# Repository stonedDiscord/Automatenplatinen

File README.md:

# Automatenplatinen
Alle möglichen Sachen die ich als Teil des Spielautomaten Hobby so nachgebaut habe.

Diskussionen rund um die Entwicklung führe ich generell auf dem Automatentreff Discord:
https://discord.gg/CEFa4MkQmW

Fertig sind:
- Initialisierer: ein Init-Stecker für weiße CPUs. Hat 2 Taster.
- ServiceTastaturWeissFake - das ist ein simpler Nachbau einer Servicetastatur für die weiße CPU. Dadurch das sie simpler ist, sind überall die Zahl 0 auf halber Helligkeit zu sehen. Verwenden lässt sie sich trotzdem.
- ZLKhalter: Anscheinend beraubt jeder, der Zulassungskarten beschreibt, einen Automaten um diesen Halter. Katastrophe.
- Zulassungskarte: Neuere mit Atmega48.

Die Gerber werde ich bei den Releases hochladen.

Ungetestet:
- FlashUniversal: Eine Pogo-Pin Platine für Datenbanken.
- LEDLamp: Das sind LEDs die in die Sockel dieser 6V 2W Glühbirnchen passen und einen Kondensator mit dabei haben damit sie langsam ausgehen wie die alten Birnen.
- LPTastatur: das ist die Tastatur für einen NSM Drucker.
- NSMAdapter: Ein Adapter der die Pins vom Timekeeper auf NSM Spielmodulen so nach außen führt das man sie mit einem EEPROM Brenner beschreiben kann.
- PCauslese: Ein Auslese-Adapter mit einem ESP-01. Soll kompatibel mit den ganz alten Geräten werden und die Uhrzeit automatisch setzen und die ausgelesenen Daten zwischenspeichern.
- ProgrammierStation: Arduino ISP Programmer und Seriell auf einem Board mit Stromversorgung.
- ST25: Tastatur für NSM Geräte
- SoundkartenProg: Ein Inverter für den seriellen Anschluss von kleinen Soundkarten.
- Tasterplatine: Fast das gleiche wie die LEDLamp aber mit einem Taster dabei. Für alte Geräte mit weißer CPU.
- Soundkarte: Ein Inverter für TTL-Signale um kleine Soundkarten auszulesen/beschreiben
- ZLKalt: Zulassungskarte mit AT90

Schrott:
- DB1MBRedesign: Forschung wo die Pins der Datenbank hingehen.
- DBV: Das ist ein Stecker der in den CPU-Sockel von Bally Wulff Spielmodulen kommt und dann die RTC und den SRAM beschreiben kann, ähnlich dem Datenbankverwalter
- E60: Hier wollt ich mal schauen wie die Konvertierung der Logik-Level umgesetzt wurde. Das Ergebnis: Ein Transistor halt. Naja.
- Programmierboard: Ein User hat das Ding auf eBay geschossen und wollte wissen was es kann.
- Serial: die ProgrammierStation aber mit WLAN, liegt auf Eis bis die normale ProgrammierStation fertig ist.
- Spielmodul: Forschung für den DBV wo die ganzen Leiterbahnen eigentlich hingehen und wie man den RTC anspricht.

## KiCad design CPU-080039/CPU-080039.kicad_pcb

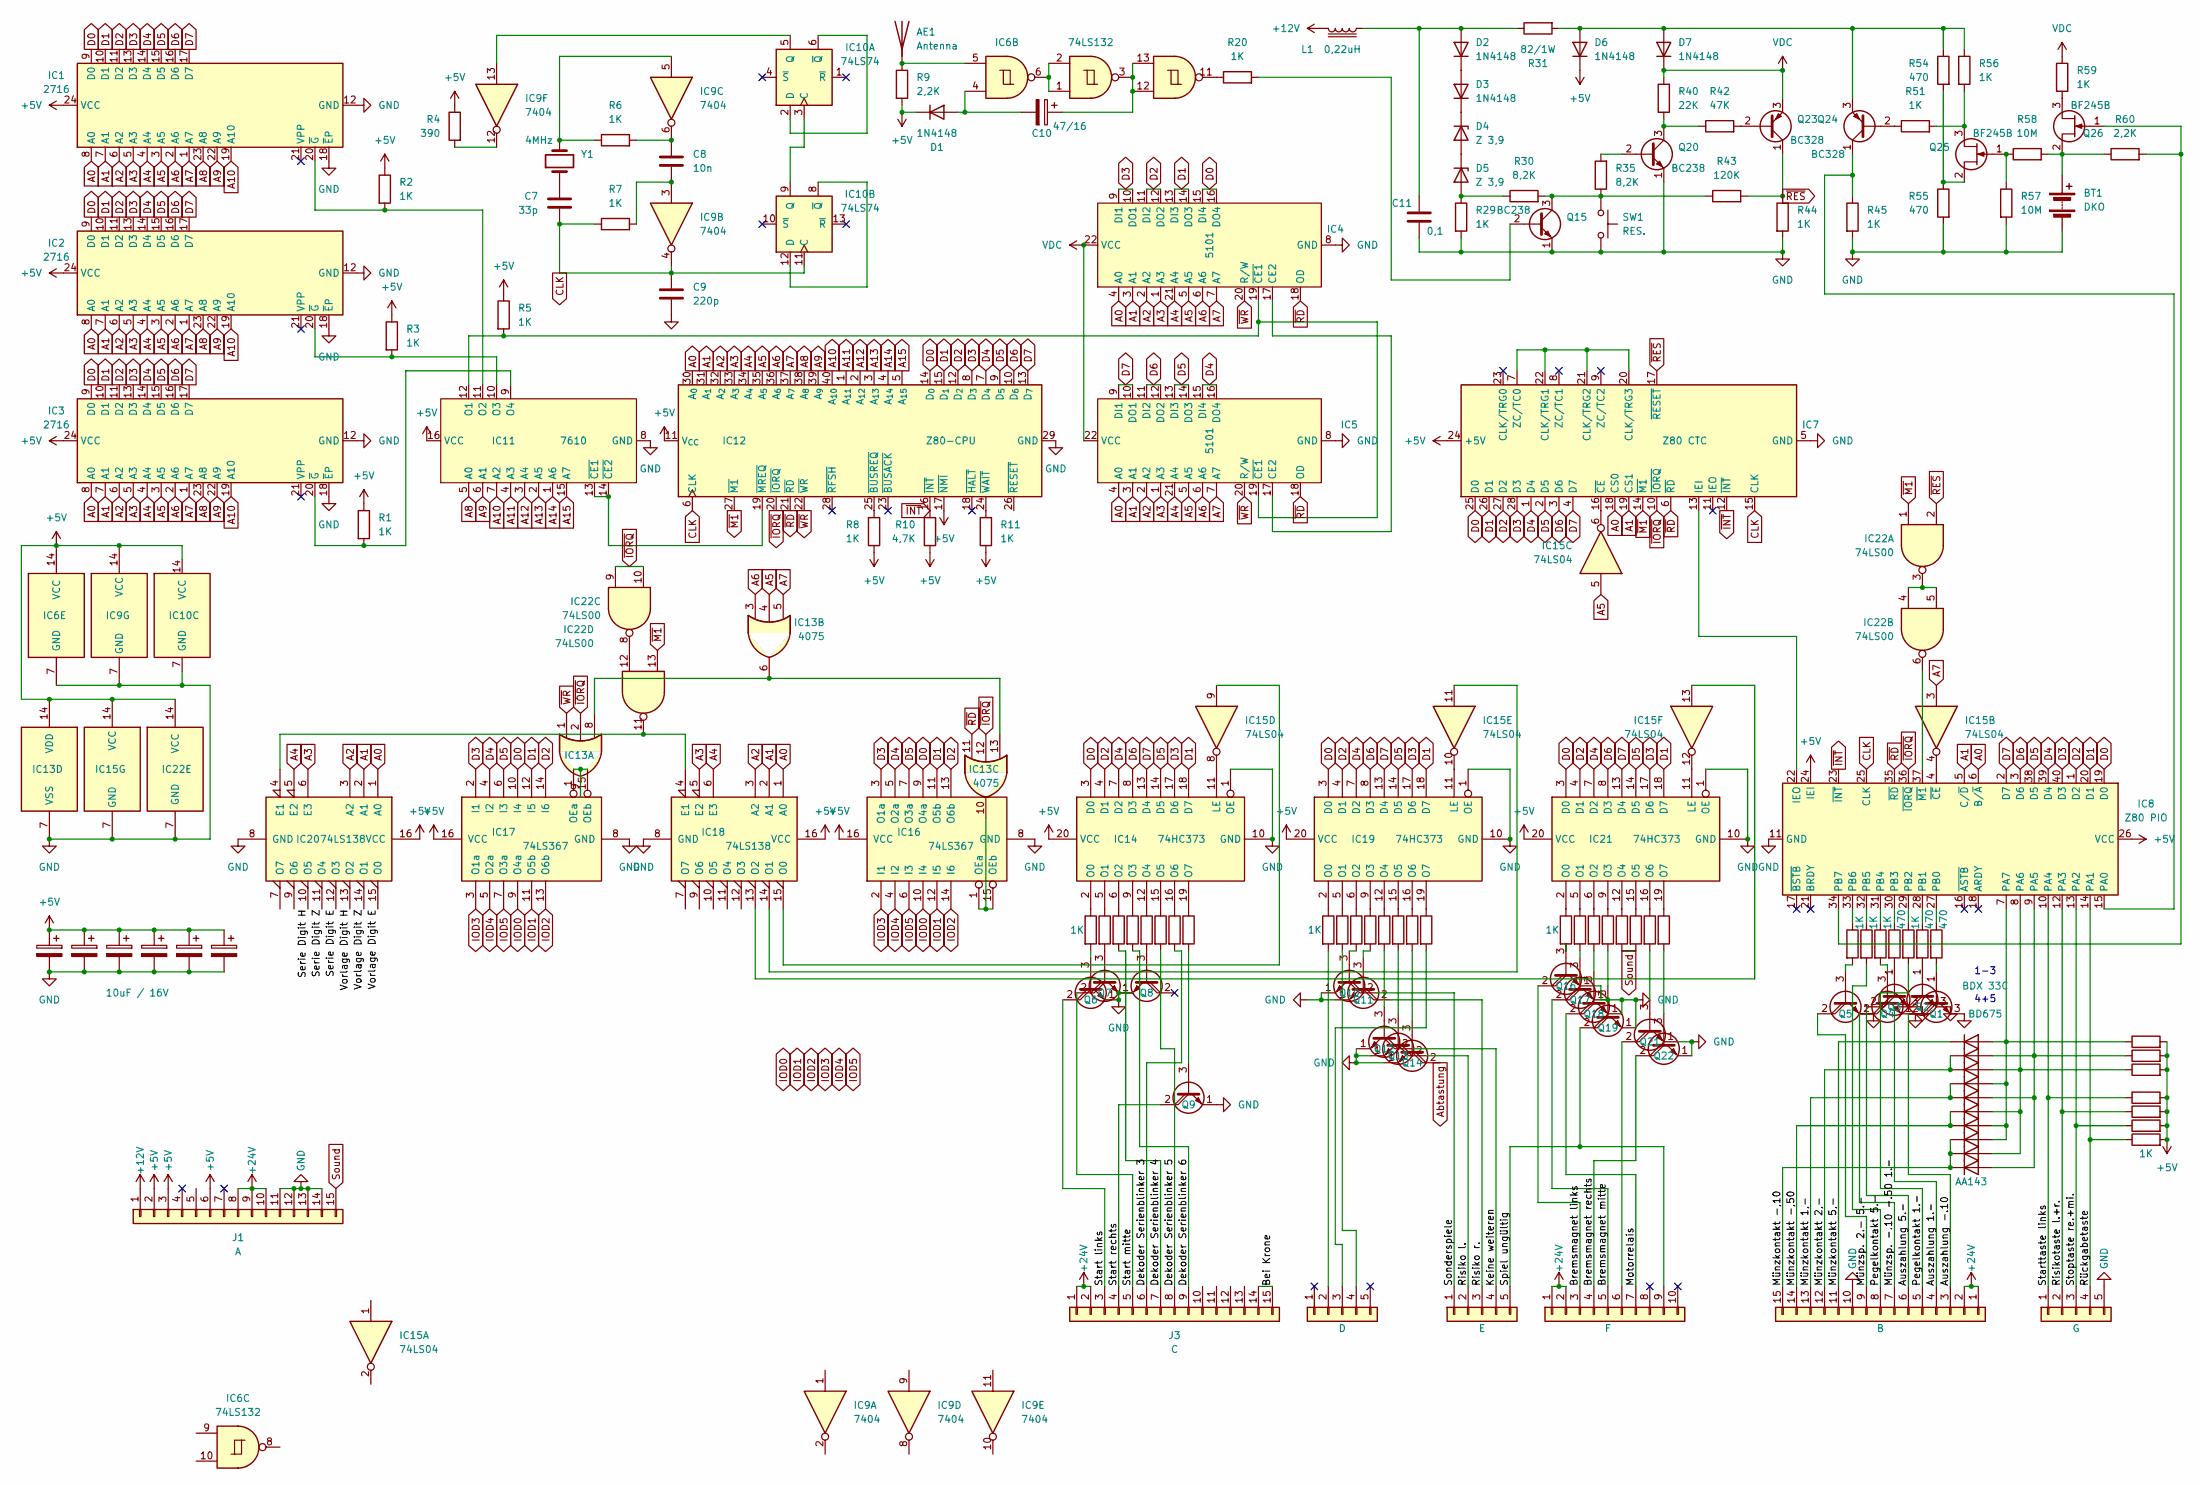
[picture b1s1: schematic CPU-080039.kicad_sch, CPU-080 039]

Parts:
AE1: Antenna
BT1: DKO
C1, C2, C3, C4, C5, C6: 10uF / 16V; CP_Radial_Tantal_D4.5mm_P5.00mm
C7: 33p; C_Disc_D4.3mm_W1.9mm_P5.00mm
C8: 10n; C_Disc_D4.3mm_W1.9mm_P5.00mm
C9: 220p; C_Disc_D4.3mm_W1.9mm_P5.00mm
C10: 47/16; C_Disc_D4.3mm_W1.9mm_P5.00mm
C11: 0,1; C_Disc_D4.3mm_W1.9mm_P5.00mm
D1, D2, D3, D6, D7: 1N4148; D_DO-35_SOD27_P12.70mm_Horizontal
D4, D5: Z 3,9; D_DO-35_SOD27_P12.70mm_Horizontal
D8, D9, D10, D11, D12, D13, D14, D15, D16, D17: AA143; D_DO-35_SOD27_P12.70mm_Horizontal
IC1, IC2, IC3: 2716; DIP-24_W15.24mm
IC4, IC5: 5101; DIP-22_W7.62mm
IC6: 74LS132; DIP-14_W7.62mm
IC7: Z80 CTC; DIP-28_W15.24mm
IC8: Z80 PIO; DIP-40_W15.24mm
IC9: 7404; DIP-14_W7.62mm
IC10: 74LS74; DIP-14_W7.62mm
IC11: 7610; DIP-16_W7.62mm
IC12: Z80-CPU; DIP-40_W15.24mm
IC13: 4075; DIP-14_W7.62mm
IC14, IC19, IC21: 74HC373; DIP-20_W7.62mm
IC15: 74LS04; DIP-14_W7.62mm
IC16, IC17: 74LS367; DIP-16_W7.62mm
IC18, IC20: 74LS138; DIP-16_W7.62mm
IC22: 74LS00; DIP-14_W7.62mm
J1: A; PinSocket_1x15_P2.54mm_Vertical
J2: B; PinSocket_1x15_P2.54mm_Vertical
J3: C; PinSocket_1x15_P2.54mm_Vertical
J4: D; PinSocket_1x05_P2.54mm_Vertical
J5: E; PinSocket_1x05_P2.54mm_Vertical
J6: F; PinSocket_1x10_P2.54mm_Vertical
J7: G; PinSocket_1x05_P2.54mm_Vertical
L1: 0,22uH; L_Axial_L6.6mm_D2.7mm_P10.16mm_Horizontal_Vishay_IM-2
Q1, Q2, Q3: BDX 33C; TO-220-3_Vertical
Q4, Q5, Q6, Q7, Q8, Q9, Q10, Q11, Q12, Q13, Q14, Q16, Q17, Q18, Q19, Q21, Q22: BD675; TO-126-3_Vertical
Q15, Q20: BC238; TO-92
Q23, Q24: BC328; TO-92
Q25, Q26: BF245B; TO-92_Inline
R1, R3, R6, R7, R8, R11, R12, R13, R14, R15, R16, R17, R18, R19, R20, R21, R22, R23, R24, R25, R26, R27, R28, R29, R32, R33, R34, R36, R37, R38, R39, R41, R44, R45, R46, R47, R48, R50, R51, R56, R59, R61, R62, R63, R64, R65, R66, R67: 1K; R_Axial_DIN0207_L6.3mm_D2.5mm_P15.24mm_Horizontal
R2, R5: 1K; R_Axial_DIN0309_L9.0mm_D3.2mm_P12.70mm_Horizontal
R4: 390; R_Axial_DIN0207_L6.3mm_D2.5mm_P15.24mm_Horizontal
R9, R60: 2,2K; R_Axial_DIN0207_L6.3mm_D2.5mm_P15.24mm_Horizontal
R10: 4,7K; R_Axial_DIN0207_L6.3mm_D2.5mm_P15.24mm_Horizontal
R30, R35: 8,2K; R_Axial_DIN0207_L6.3mm_D2.5mm_P15.24mm_Horizontal
R31: 82/1W; R_Axial_DIN0309_L9.0mm_D3.2mm_P25.40mm_Horizontal
R40: 22K; R_Axial_DIN0207_L6.3mm_D2.5mm_P15.24mm_Horizontal
R42: 47K; R_Axial_DIN0207_L6.3mm_D2.5mm_P15.24mm_Horizontal
R43: 120K; R_Axial_DIN0207_L6.3mm_D2.5mm_P15.24mm_Horizontal
R49, R52, R53, R54, R55: 470; R_Axial_DIN0207_L6.3mm_D2.5mm_P15.24mm_Horizontal
R57, R58: 10M; R_Axial_DIN0207_L6.3mm_D2.5mm_P15.24mm_Horizontal
SW1: RES.; SW_PUSH-12mm
Y1: 4MHz; Crystal_HC18-U_Vertical

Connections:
+5V: C1.1, C2.1, C3.1, C4.1, C5.1, C6.1, D1.1 (K), D6.1 (K), IC1.24 (VCC), IC2.24 (VCC), IC3.24 (VCC), IC6.14 (VCC), IC7.24 (+5V), IC8.24 (IEI), IC8.26 (VCC), IC9.14 (VCC), IC10.14 (VCC), IC11.16 (VCC), IC12.11 (V_{CC}), IC12.17 (~NMI), IC13.14 (VDD), IC14.20 (VCC), IC15.14 (VCC), IC16.16 (VCC), IC17.16 (VCC), IC18.16 (VCC), IC19.20 (VCC), IC20.16 (VCC), IC21.20 (VCC), IC22.14 (VCC), J1.2, J1.3, J1.6, R1.1, R2.1, R3.1, R4.1, R5.1, R8.1, R9.2, R10.1, R11.1, R61.2, R62.2, R63.2, R64.2, R65.2, R66.2, R67.2
+12V: J1.1, L1.2
+24V: J1.8, J1.9, J1.10, J2.1, J2.2, J3.1, J3.2, J6.1, J6.2
/Auszahlung 1.-: J2.4, Q2.2 (C)
/Auszahlung 5.-: J2.6, Q3.2 (C)
/Auszahlung -.10: J2.3, Q1.2 (C)
/Bei Krone: J3.14, J3.15
/Bremsmagnet links: J6.3, Q16.2 (C)
/Bremsmagnet mitte: J6.5, Q17.2 (C)
/Bremsmagnet rechts: J6.4, Q22.2 (C)
/Dekoder Serienblinker 3: J3.6, R18.2
/Dekoder Serienblinker 4: J3.7, R14.2
/Dekoder Serienblinker 5: J3.8, R17.2
/Dekoder Serienblinker 6: J3.9, R15.2
/Keine weiteren: J5.4, Q12.2 (C)
/Motorrelais: J6.7, Q18.2 (C)
/Münzkontakt 1,-: D11.1 (K), D12.1 (K), J2.13
/Münzkontakt 2,-: D9.1 (K), D10.1 (K), J2.12
/Münzkontakt 5,-: D8.1 (K), J2.11
/Münzkontakt -,10: D15.1 (K), D16.1 (K), D17.1 (K), J2.15
/Münzkontakt -,50: D13.1 (K), D14.1 (K), J2.14
/Münzsp. 2.- 5.-: J2.9, Q5.2 (C)
/Münzsp. -.10 -.50 1.-: J2.7, Q4.2 (C)
/Pegelkontakt 1.-: J2.5, R50.2
/Pegelkontakt 5.-: J2.8, R47.2
/Risiko l.: J5.2, Q13.2 (C)
/Risiko r.: J5.3, Q11.2 (C)
/Risikotaste l.+r.: IC8.12 (PA3), J7.2, R65.1
/Rückgabetaste: IC8.14 (PA1), J7.4, R67.1
/Serie Digit E: IC20.12 (O3)
/Serie Digit H: IC20.10 (O5)
/Serie Digit Z: IC20.11 (O4)
/Sonderspiele: J5.1, Q10.2 (C)
/Spiel ungültig: J5.5, J6.9, Q19.2 (C)
/Start links: J3.3, Q6.2 (C)
/Start mitte: J3.5, Q7.2 (C)
/Start rechts: J3.4, Q9.2 (C)
/Starttaste links: IC8.10 (PA4), J7.1, R64.1
/Stoptaste re.+mi.: IC8.13 (PA2), J7.3, R66.1
/Vorlage Digit E: IC20.15 (O0)
/Vorlage Digit H: IC20.13 (O2)
/Vorlage Digit Z: IC20.14 (O1)
A0: IC1.8 (A0), IC2.8 (A0), IC3.8 (A0), IC4.4 (A0), IC5.4 (A0), IC7.18 (CS0), IC8.6 (B/~A), IC12.30 (A_{0}), IC18.1 (A0), IC20.1 (A0)
A1: IC1.7 (A1), IC2.7 (A1), IC3.7 (A1), IC4.3 (A1), IC5.3 (A1), IC7.19 (CS1), IC8.5 (C/~D), IC12.31 (A_{1}), IC18.2 (A1), IC20.2 (A1)
A2: IC1.6 (A2), IC2.6 (A2), IC3.6 (A2), IC4.2 (A2), IC5.2 (A2), IC12.32 (A_{2}), IC18.3 (A2), IC20.3 (A2)
A3: IC1.5 (A3), IC2.5 (A3), IC3.5 (A3), IC4.1 (A3), IC5.1 (A3), IC12.33 (A_{3}), IC18.5 (E2), IC20.6 (E3)
A4: IC1.4 (A4), IC2.4 (A4), IC3.4 (A4), IC4.21 (A4), IC5.21 (A4), IC12.34 (A_{4}), IC18.6 (E3), IC20.5 (E2)
A5: IC1.3 (A5), IC2.3 (A5), IC3.3 (A5), IC4.5 (A5), IC5.5 (A5), IC12.35 (A_{5}), IC13.4, IC15.5
A6: IC1.2 (A6), IC2.2 (A6), IC3.2 (A6), IC4.6 (A6), IC5.6 (A6), IC12.36 (A_{6}), IC13.3
A7: IC1.1 (A7), IC2.1 (A7), IC3.1 (A7), IC4.7 (A7), IC5.7 (A7), IC12.37 (A_{7}), IC13.5, IC15.3
A8: IC1.23 (A8), IC2.23 (A8), IC3.23 (A8), IC11.5 (A0), IC12.38 (A_{8})
A9: IC1.22 (A9), IC2.22 (A9), IC3.22 (A9), IC11.6 (A1), IC12.39 (A_{9})
A10: IC1.19 (A10), IC2.19 (A10), IC3.19 (A10), IC11.7 (A2), IC12.40 (A_{10})
A11: IC11.4 (A3), IC12.1 (A_{11})
A12: IC11.3 (A4), IC12.2 (A_{12})
A13: IC11.2 (A5), IC12.3 (A_{13})
A14: IC11.1 (A6), IC12.4 (A_{14})
A15: IC11.15 (A7), IC12.5 (A_{15})
Abtastung: Q14.2 (C)
CLK: C7.2, C9.1, IC7.15 (CLK), IC8.25 (CLK), IC9.4, IC10.11 (C), IC12.6 (CLK), R7.1
D0: IC1.9 (D0), IC2.9 (D0), IC3.9 (D0), IC4.15 (DI4), IC4.16 (DO4), IC7.25 (D0), IC8.19 (D0), IC12.14 (D_{0}), IC14.3 (D0), IC16.9 (O4a), IC17.10 (I4), IC19.3 (D0), IC21.3 (D0)
D1: IC1.10 (D1), IC2.10 (D1), IC3.10 (D1), IC4.13 (DI3), IC4.14 (DO3), IC7.26 (D1), IC8.20 (D1), IC12.15 (D_{1}), IC14.18 (D7), IC16.11 (O5b), IC17.12 (I5), IC19.18 (D7), IC21.18 (D7)
D2: IC1.11 (D2), IC2.11 (D2), IC3.11 (D2), IC4.11 (DI2), IC4.12 (DO2), IC7.27 (D2), IC8.1 (D2), IC12.12 (D_{2}), IC14.4 (D1), IC16.13 (O6b), IC17.14 (I6), IC19.4 (D1), IC21.4 (D1)
D3: IC1.13 (D3), IC2.13 (D3), IC3.13 (D3), IC4.9 (DI1), IC4.10 (DO1), IC7.28 (D3), IC8.40 (D3), IC12.8 (D_{3}), IC14.17 (D6), IC16.3 (O1a), IC17.2 (I1), IC19.17 (D6), IC21.17 (D6)
D4: IC1.14 (D4), IC2.14 (D4), IC3.14 (D4), IC5.15 (DI4), IC5.16 (DO4), IC7.1 (D4), IC8.39 (D4), IC12.7 (D_{4}), IC14.7 (D2), IC16.5 (O2a), IC17.4 (I2), IC19.7 (D2), IC21.7 (D2)
D5: IC1.15 (D5), IC2.15 (D5), IC3.15 (D5), IC5.13 (DI3), IC5.14 (DO3), IC7.2 (D5), IC8.38 (D5), IC12.9 (D_{5}), IC14.14 (D5), IC16.7 (O3a), IC17.6 (I3), IC19.14 (D5), IC21.14 (D5)
D6: IC1.16 (D6), IC2.16 (D6), IC3.16 (D6), IC5.11 (DI2), IC5.12 (DO2), IC7.3 (D6), IC8.3 (D6), IC12.10 (D_{6}), IC14.8 (D3), IC19.8 (D3), IC21.8 (D3)
D7: IC1.17 (D7), IC2.17 (D7), IC3.17 (D7), IC5.9 (DI1), IC5.10 (DO1), IC7.4 (D7), IC8.2 (D7), IC12.13 (D_{7}), IC14.13 (D4), IC19.13 (D4), IC21.13 (D4)
GND: BT1.2 (-), C1.2, C2.2, C3.2, C4.2, C5.2, C6.2, C9.2, C11.2, IC1.12 (GND), IC1.18 (~EP), IC2.12 (GND), IC2.18 (~EP), IC3.12 (GND), IC3.18 (~EP), IC4.8 (GND), IC5.8 (GND), IC6.7 (GND), IC7.5 (GND), IC8.11 (GND), IC9.7 (GND), IC10.7 (GND), IC11.8 (GND), IC12.29 (GND), IC13.7 (VSS), IC14.1 (OE), IC14.10 (GND), IC15.7 (GND), IC16.8 (GND), IC17.8 (GND), IC18.8 (GND), IC19.1 (OE), IC19.10 (GND), IC20.8 (GND), IC21.1 (OE), IC21.10 (GND), IC22.7 (GND), J1.11, J1.12, J1.13, J1.14, J2.10, J7.5, Q1.3 (E), Q2.3 (E), Q3.3 (E), Q4.1 (E), Q5.1 (E), Q6.1 (E), Q7.1 (E), Q8.1 (E), Q9.1 (E), Q10.1 (E), Q11.1 (E), Q12.1 (E), Q13.1 (E), Q14.1 (E), Q15.1 (E), Q16.1 (E), Q17.1 (E), Q18.1 (E), Q19.1 (E), Q20.1 (E), Q21.1 (E), Q22.1 (E), R29.2, R44.2, R45.2, R55.2, R57.2, SW1.2
IOD0: IC16.10 (I4), IC17.9 (O4a)
IOD1: IC16.12 (I5), IC17.11 (O5b)
IOD2: IC16.14 (I6), IC17.13 (O6b)
IOD3: IC16.2 (I1), IC17.3 (O1a)
IOD4: IC16.4 (I2), IC17.5 (O2a)
IOD5: IC16.6 (I3), IC17.7 (O3a)
unnamed: AE1.1, IC6.5, R9.1
unnamed: BT1.1 (+), Q26.2 (S), R58.2, R60.1
unnamed: C7.1, Y1.1
unnamed: C8.1, IC9.6, R6.2
unnamed: C8.2, IC9.3, R7.2
unnamed: C10.1, IC6.3, IC6.12, IC6.13
unnamed: C10.2, D1.2 (A), IC6.4
unnamed: C11.1, D2.2 (A), L1.1, R31.1
unnamed: D2.1 (K), D3.2 (A)
unnamed: D3.1 (K), D4.1 (K)
unnamed: D4.2 (A), D5.1 (K)
unnamed: D5.2 (A), R29.1, R30.1
unnamed: D6.2 (A), D7.2 (A), Q24.3 (E), R31.2, R54.1, R56.1
unnamed: D10.2 (A), D13.2 (A), D16.2 (A), IC8.8 (PA6), R63.1
unnamed: D8.2 (A), D11.2 (A), D14.2 (A), D15.2 (A), IC8.7 (PA7), R61.1
unnamed: D9.2 (A), D12.2 (A), D17.2 (A), IC8.9 (PA5), R62.1
unnamed: IC1.20 (~G), IC11.11 (O2), R2.2
unnamed: IC4.17 (CE2), IC5.17 (CE2)
unnamed: IC6.1, IC6.2, IC6.6
unnamed: IC6.11, R20.1
unnamed: IC7.7 (ZC/TC0), IC7.20 (CLK/TRG3), IC7.21 (CLK/TRG2), IC7.22 (CLK/TRG1)
unnamed: IC7.13 (IEI), IC8.22 (IEO)
unnamed: IC7.16 (~CE), IC15.6
unnamed: IC8.15 (PA0), Q24.1 (C), R45.1
unnamed: IC8.27 (PB0), R53.1
unnamed: IC8.28 (PB1), R52.1
unnamed: IC8.29 (PB2), R50.1
unnamed: IC8.30 (PB3), R49.1
unnamed: IC8.31 (PB4), R48.1
unnamed: IC8.32 (PB5), R47.1
unnamed: IC8.33 (PB6), R46.1
unnamed: IC8.34 (PB7), Q26.1 (G), R60.2
unnamed: IC8.4 (~CE), IC15.4
unnamed: IC8.37 (~M1), IC22.6
unnamed: IC9.5, R6.1, Y1.2
unnamed: IC9.12, R4.2
unnamed: IC10.3 (C), IC10.9 (Q)
unnamed: IC10.2 (D), IC10.6 (~Q)
unnamed: IC9.13, IC10.5 (Q)
unnamed: IC10.8 (~Q), IC10.12 (D)
unnamed: IC4.19 (~CE1), IC5.19 (~CE1), IC11.12 (O1), R5.2
unnamed: IC2.20 (~G), IC11.10 (O3), R3.2
unnamed: IC3.20 (~G), IC11.9 (O4), R1.2
unnamed: IC11.13 (~CE1), IC11.14 (~CE2), IC12.19 (~MREQ)
unnamed: IC12.25 (~BUSREQ), R8.2
unnamed: IC12.24 (~WAIT), R11.2
unnamed: IC13.6, IC13.8, IC13.13
unnamed: IC14.11 (LE), IC15.8
unnamed: IC14.2 (O0), R12.1
unnamed: IC14.5 (O1), R13.1
unnamed: IC14.6 (O2), R14.1
unnamed: IC14.9 (O3), R15.1
unnamed: IC14.12 (O4), R16.1
unnamed: IC14.15 (O5), R17.1
unnamed: IC14.16 (O6), R18.1
unnamed: IC14.19 (O7), R19.1
unnamed: IC13.10, IC16.1 (OEa), IC16.15 (OEb)
unnamed: IC13.9, IC17.1 (OEa), IC17.15 (OEb)
unnamed: IC18.4 (E1), IC20.4 (E1), IC22.11
unnamed: IC15.9, IC18.15 (O0)
unnamed: IC15.11, IC18.14 (O1)
unnamed: IC15.13, IC18.13 (O2)
unnamed: IC15.10, IC19.11 (LE)
unnamed: IC19.2 (O0), R21.1
unnamed: IC19.5 (O1), R22.1
unnamed: IC19.6 (O2), R23.1
unnamed: IC19.9 (O3), R24.1
unnamed: IC19.12 (O4), R25.1
unnamed: IC19.15 (O5), R26.1
unnamed: IC19.16 (O6), R27.1
unnamed: IC19.19 (O7), R28.1
unnamed: IC15.12, IC21.11 (LE)
unnamed: IC21.2 (O0), R32.1
unnamed: IC21.5 (O1), R33.1
unnamed: IC21.6 (O2), R34.1
unnamed: IC21.9 (O3), R36.1
unnamed: IC21.12 (O4), R37.1
unnamed: IC21.15 (O5), R38.1
unnamed: IC21.16 (O6), R39.1
unnamed: IC21.19 (O7), R41.1
unnamed: IC22.3, IC22.4, IC22.5
unnamed: IC22.8, IC22.12
unnamed: J4.2, R21.2
unnamed: J4.3, R28.2
unnamed: J4.4, R22.2
unnamed: J6.6, Q21.2 (C)
unnamed: Q1.1 (B), R53.2
unnamed: Q2.1 (B), R52.2
unnamed: Q3.1 (B), R49.2
unnamed: Q4.3 (B), R48.2
unnamed: Q5.3 (B), R46.2
unnamed: Q6.3 (B), R12.2
unnamed: Q7.3 (B), R13.2
unnamed: Q8.3 (B), R16.2
unnamed: Q9.3 (B), R19.2
unnamed: Q10.3 (B), R23.2
unnamed: Q11.3 (B), R24.2
unnamed: Q12.3 (B), R25.2
unnamed: Q13.3 (B), R26.2
unnamed: Q14.3 (B), R27.2
unnamed: Q15.2 (B), R20.2
unnamed: Q15.3 (C), R30.2, R35.1, R43.1, SW1.1
unnamed: Q16.3 (B), R32.2
unnamed: Q17.3 (B), R33.2
unnamed: Q18.3 (B), R34.2
unnamed: Q19.3 (B), R36.2
unnamed: Q20.2 (B), R35.2
unnamed: Q20.3 (C), R40.1, R42.1
unnamed: Q21.3 (B), R39.2
unnamed: Q22.3 (B), R41.2
unnamed: Q23.2 (B), R42.2
unnamed: Q24.2 (B), R51.1
unnamed: Q25.3 (D), R51.2, R56.2
unnamed: Q25.1 (G), R57.1, R58.1
unnamed: Q25.2 (S), R54.2, R55.1
unnamed: Q26.3 (D), R59.2
Sound: J1.15, R37.2, R38.2
VDC: D7.1 (K), IC4.22 (VCC), IC5.22 (VCC), Q23.3 (E), R40.2, R59.1
~INT: IC7.12 (~INT), IC8.23 (~INT), IC12.16 (~INT), R10.2
~IORQ: IC7.10 (~IORQ), IC8.36 (~IORQ), IC12.20 (~IORQ), IC13.2, IC13.12, IC22.9, IC22.10
~M1: IC7.14 (~M1), IC12.27 (~M1), IC22.1, IC22.13
~RD: IC4.18 (OD), IC5.18 (OD), IC7.6 (~RD), IC8.35 (~RD), IC12.21 (~RD), IC13.11
~RES: IC7.17 (~RESET), IC22.2, Q23.1 (C), R43.2, R44.1
~WR: IC4.20 (R/W), IC5.20 (R/W), IC12.22 (~WR), IC13.1

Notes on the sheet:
4+5
1-3

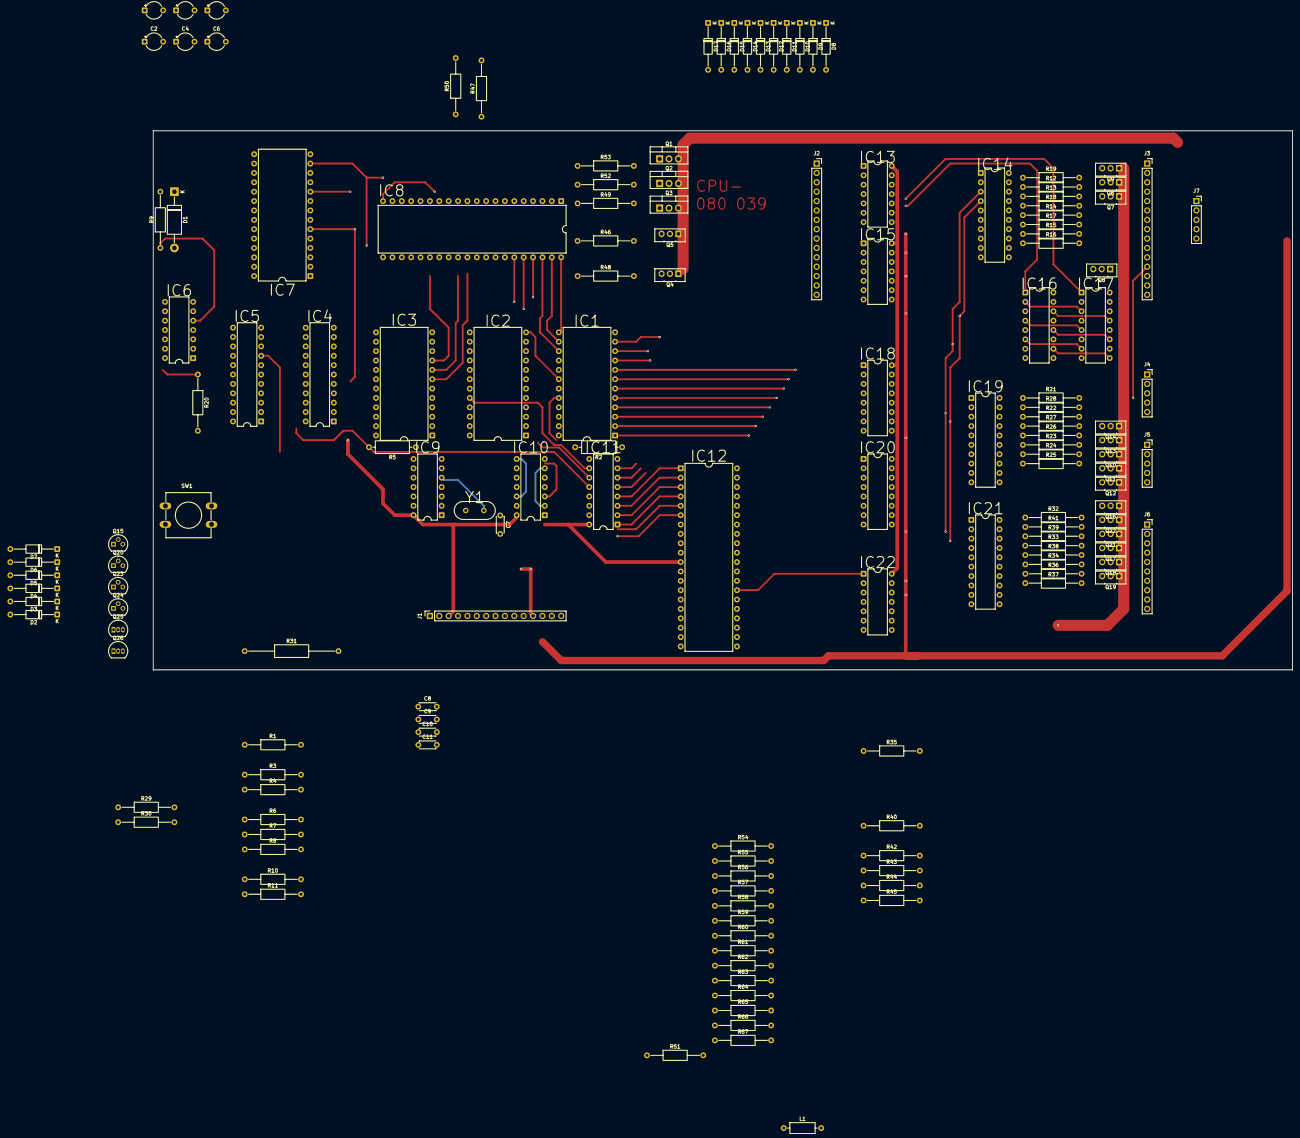
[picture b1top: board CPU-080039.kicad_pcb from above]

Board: 2 copper layers, 308.6 x 146.1 mm, 153 parts (0 on the bottom side), 192 nets.
